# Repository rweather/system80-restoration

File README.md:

Dick Smith System 80 Restoration
================================

This repository chronicles my exploits in restoring a Dick Smith System 80
that I got off eBay.

## Technical specifications

* Z-80 8-bit CPU, running at 1.77MHz.
* 12K of ROM containing BASIC.
* 1K of video RAM for 64 x 16 text mode or 128 x 48 graphics mode.
* 16K of user program RAM, expandable to 48K using an expansion module.

### Initial condition of the unit

According to the seller on eBay, the unit had been sitting in a shed for
30+ years.  The original owner is into boating.  I'm guessing the shed
was near the seaside from the corrosion inside!

The unit was in pretty rough shape cosmetically.  Lots of dirt, cable burns,
missing cassette stickers for play/pause/stop/etc, and broken pieces in the
ventilation at the back (right-click and open in a new tab for a
larger version):

The bottom was in relatively good condition with some cable burns
The nameplate sticker was missing but the serial number and QA stickers
were still present.  Serial number 281001.

Here are some closeups of the outside:

Inside was a lot of dirt and rust!

The cassette mechanism was completely rusted out and the motor was seized up.
Not sure what I can do about this at the moment.

### Cleaning

I pulled everything apart and cleaned the case and keyboard as best
as possible.  Something needs to be done about the cable burns and the
broken pieces later.

### Chip testing

Next, I pulled all of the chips that were in sockets and ran them through my
[BackBit Chip Tester Pro V2](https://store.backbit.io/product/chip-tester/).

Main board:

* Z5 - Z-80 CPU - Failed with "BAD ADDR" error.  I already had a replacement.
* Z10 - E3001 BASIC ROM - Good when tested with chip type "2332".
* Z11 - E3002 BASIC ROM - Good when tested with chip type "2332".
* Z12 - E3003 BASIC ROM - Good when tested with chip type "2332".
* Z27 - HM4716AP-4N 16Kx1 Dynamic RAM - Not testable.
* Z28 - HM4716AP-4N 16Kx1 Dynamic RAM - Not testable.
* Z29 - HM4716AP-4N 16Kx1 Dynamic RAM - Not testable.
* Z30 - HM4716AP-4N 16Kx1 Dynamic RAM - Not testable.
* Z31 - HM4716AP-4N 16Kx1 Dynamic RAM - Not testable.
* Z32 - HM4716AP-4N 16Kx1 Dynamic RAM - Not testable.
* Z33 - HM4716AP-4N 16Kx1 Dynamic RAM - Not testable.
* Z34 - HM4716AP-4N 16Kx1 Dynamic RAM - Not testable.

I wasn't able to test the DRAM chips because I need an adapter to provide the
-5V and +12V supply rails, which I do not presently have.  But since BASIC
ran fine later (see below), I'm guessing the DRAM's are ok.

Video board:

* Z17 - MM2114-N 1Kx4 Static RAM - Good.
* Z18 - MM2114-N 1Kx4 Static RAM - Good.
* Z25 - 52116 Character Generator ROM - Good when tested with chip type "2532".

The dumped ROM images are in the `ROMs` directory of this repository.

In the process of inspecting the PCB's and testing the chips, I found a
dead bug hiding under one of the capacitors.  Which I removed of course.
Don't want the bug causing issues for me later like the
[world's first computer bug](https://www.computerhistory.org/tdih/september/9/).

## Recapping the power supply

This was the initial state of the power supply:

Other than the dirt, the only glaring issue was the three big electrolytic
capacitors.  The date codes on the chips on the motherboard are from 1981,
so these capacitors are around 45 years old.  I didn't even bother to
test them - I just replaced them.

The three original capacitors were:

* 22000uF, 16V - replaced with two 10000uF, 16V capacitors in parallel.
* 2200uF, 25V
* 1000uF, 25V

The voltage outputs seemed fine if a little high.  Probably due to no load.
It was time to power on the main PCB's.

## Power on smoke test

I reconnected everything except the cassette deck, crossed my fingers,
and turned it on.  The LED's on either side of the keyboard turned on.
That's a good sign.

The 5V rail on the CPU board was 5.05V.  On the video board it was 4.99V.
12V rail was 12.15V.  -5V rail was -5.06V.  Perfect.

The 10.64MHz crystal was oscillating at 10.64MHz according to my
oscilloscope.  Also perfect.

The ROM chips were running a little hot.  Not sure if that is a problem
or not yet.

I could see a composite video signal of some sort on the monitor output
port with my oscilloscope.  But my RetroTink had difficulty locking
onto the signal to display an image.  Then I saw a "Ready?" prompt!  Yay!

The video cuts in and out which is very annoying, but I was able to test
the keyboard.  Some of the keys don't work or are intermittent and bouncy.
I did manage to type a simple `10 PRINT "HELLO WORLD"` program once,
but didn't get a photo.  Some keys like T and N only work now and then.

### What's working so far?

* Power supply.
* Z-80 CPU (after I replaced it as described above).
* BASIC ROM's.
* 16K of dynamic RAM on the CPU board.
* 1K of static RAM on the video board.
* Video circuitry for HSYNC/VSYNC and video memory address generation.
* Character generator ROM.
* Composite video output.
* Most keys on the keyboard work, but some keys are flaky.

### In-depth testing and fault finding

Next steps:

* The video signal is not stable; it cuts in and out.
* Deal with the keys on the keyboard that are intermittent or bouncy.
* ROM's run a little hot.  Probably OK.
* Deal with the corrosion on the expansion port connector and keyboard.
* Deal with the cassette deck - it may be a lost cause.

### Flaky video signal

My brother found a composite-to-RGB converter for cheap at an end of
financial year sale for a local electronics retailer.  The composite-to-RGB
converter didn't work with other computers like my Dick Smith Cat,
but it worked perfectly with the System 80!

It looks like the video problem was with the RetroTink all along,
not with the System 80.

The video is a little shaky, but I can live with it for now.

### Non-working keys on the keyboard

I found the problem with the keyboard.  With all of the handling of the PCB,
metal fatigue in the wires built up and snapped two of the wires on the
keyboard ribbon cable (right-click and open in a new tab for a larger version):

This type of soldered ribbon cable is a real pain in the neck.
Even minor board handling will tear them off if you aren't careful.
There were similar cables on
[a VZ200 and a VZ300 that I restored previously](https://github.com/rweather/vz200-restoration).

Those two wires correspond to the columns containing the intermittent
keys like N and T.  No wonder I was having problems typing "PRINT" in BASIC.
I was able to type in a "HELLO WORLD" BASIC program just one time.
I guess the cable was angled to make the wires touch briefly that one time.

I replaced the cable with something easier to repair in the future if a
wire comes loose:

I then tested all of the keys.  Some of them were very flaky.  Testing
them with a multimeter showed some at 20 Mohms when pressed.  Probably
corrosion in the contacts.  I pounded the keys a few dozen times and
they came good!

Some keys like N and I are still a little bouncy, but as long as I don't
type too fast they are ok.  Unfortunately, my natural typing speed is fast!

### Summary of changes made

Here is a summary of the changes that I made:

* Cleaned the case, keyboard, PCB's, etc.
* Replaced the filter capacitors in the power supply.
* Replaced the Z-80 CPU with a new one, as the original was broken.
* Desoldered the RF video cable from the RF modulator.  Analog television
  sets are very rare these days and composite video works fine.
* Modified the keyboard ribbon cable and connectors to be easily repairable.

Costs (in AUD):

* $500 for the System 80 off eBay.
* $27 to replace the filter capacitors in the power supply.

## Schematics

I have reproduced some of the schematics from the Technical Manual in KiCad
and generated PDF versions.  The original schematics can be hard to read.

* [System 80 Main Board](schematics/System_80_Main_Board/PDF/System_80_Main_Board.pdf)
* [System 80 Video / Cassette Board](schematics/System_80_Video_Cassette/PDF/System_80_Video_Cassette.pdf)
* [System 80 Power Supply](schematics/System_80_Power_Supply/PDF/System_80_Power_Supply.pdf)
* [System 80 Keyboard](schematics/System_80_Keyboard/PDF/System_80_Keyboard.pdf)

## Expansion options

I designed a [Memory Cartridge](memory_cartridge.md) for the System 80
that plugs into the expanion bus.  It provides either 32K of extra RAM,
or 16K of RAM plus 16K of EEPROM.

## Adapting the schematic

In theory the KiCad schematics could be modernised and then laid out on
brand new PCB's.  But a lot of work would be required to add footprints
and lay everything out.

The components in the System 80 are mostly bog-standard Z-80, memory, and
TTL logic chips that can still be sourced today.  The main exception is
the character generator ROM, but that could be replaced with a modern EEPROM.

Making a new System 80 from scratch wouldn't be difficult.  But some things
would be easier with modern components:

* Use a single 16K EEPROM instead of separate 4K EPROM's.
* Use static RAM chips like the 32K 62256 for system memory, instead of
dynamic RAM.  This removes a lot of complexity from the memory interface.
* Replace the 6-way 74LS367 bus transceivers with the 8-way 74LS244 and
74LS245 instead to reduce the number of transceiver chips.
* Replace the 5-pin composite video connector with a standard RCA jack.
* Replace the character generator ROM with a modern EEPROM and include the
graphics characters in the EEPROM.  This removes the need for a separate
circuit for rendering the graphics characters.

## License

<p xmlns:cc="http://creativecommons.org/ns#" xmlns:dct="http://purl.org/dc/terms/"><span property="dct:title">System 80 Restoration</span> by <span property="cc:attributionName">Rhys Weatherley</span> is licensed under <a href="http://creativecommons.org/licenses/by-nc-sa/4.0/?ref=chooser-v1" target="_blank" rel="license noopener noreferrer" style="display:inline-block;">Attribution-NonCommercial-ShareAlike 4.0 International</a></p>

## Contact

For more information on this project, to report bugs, or to suggest
improvements, please contact the author Rhys Weatherley via
[email](mailto:rhys.weatherley@gmail.com).

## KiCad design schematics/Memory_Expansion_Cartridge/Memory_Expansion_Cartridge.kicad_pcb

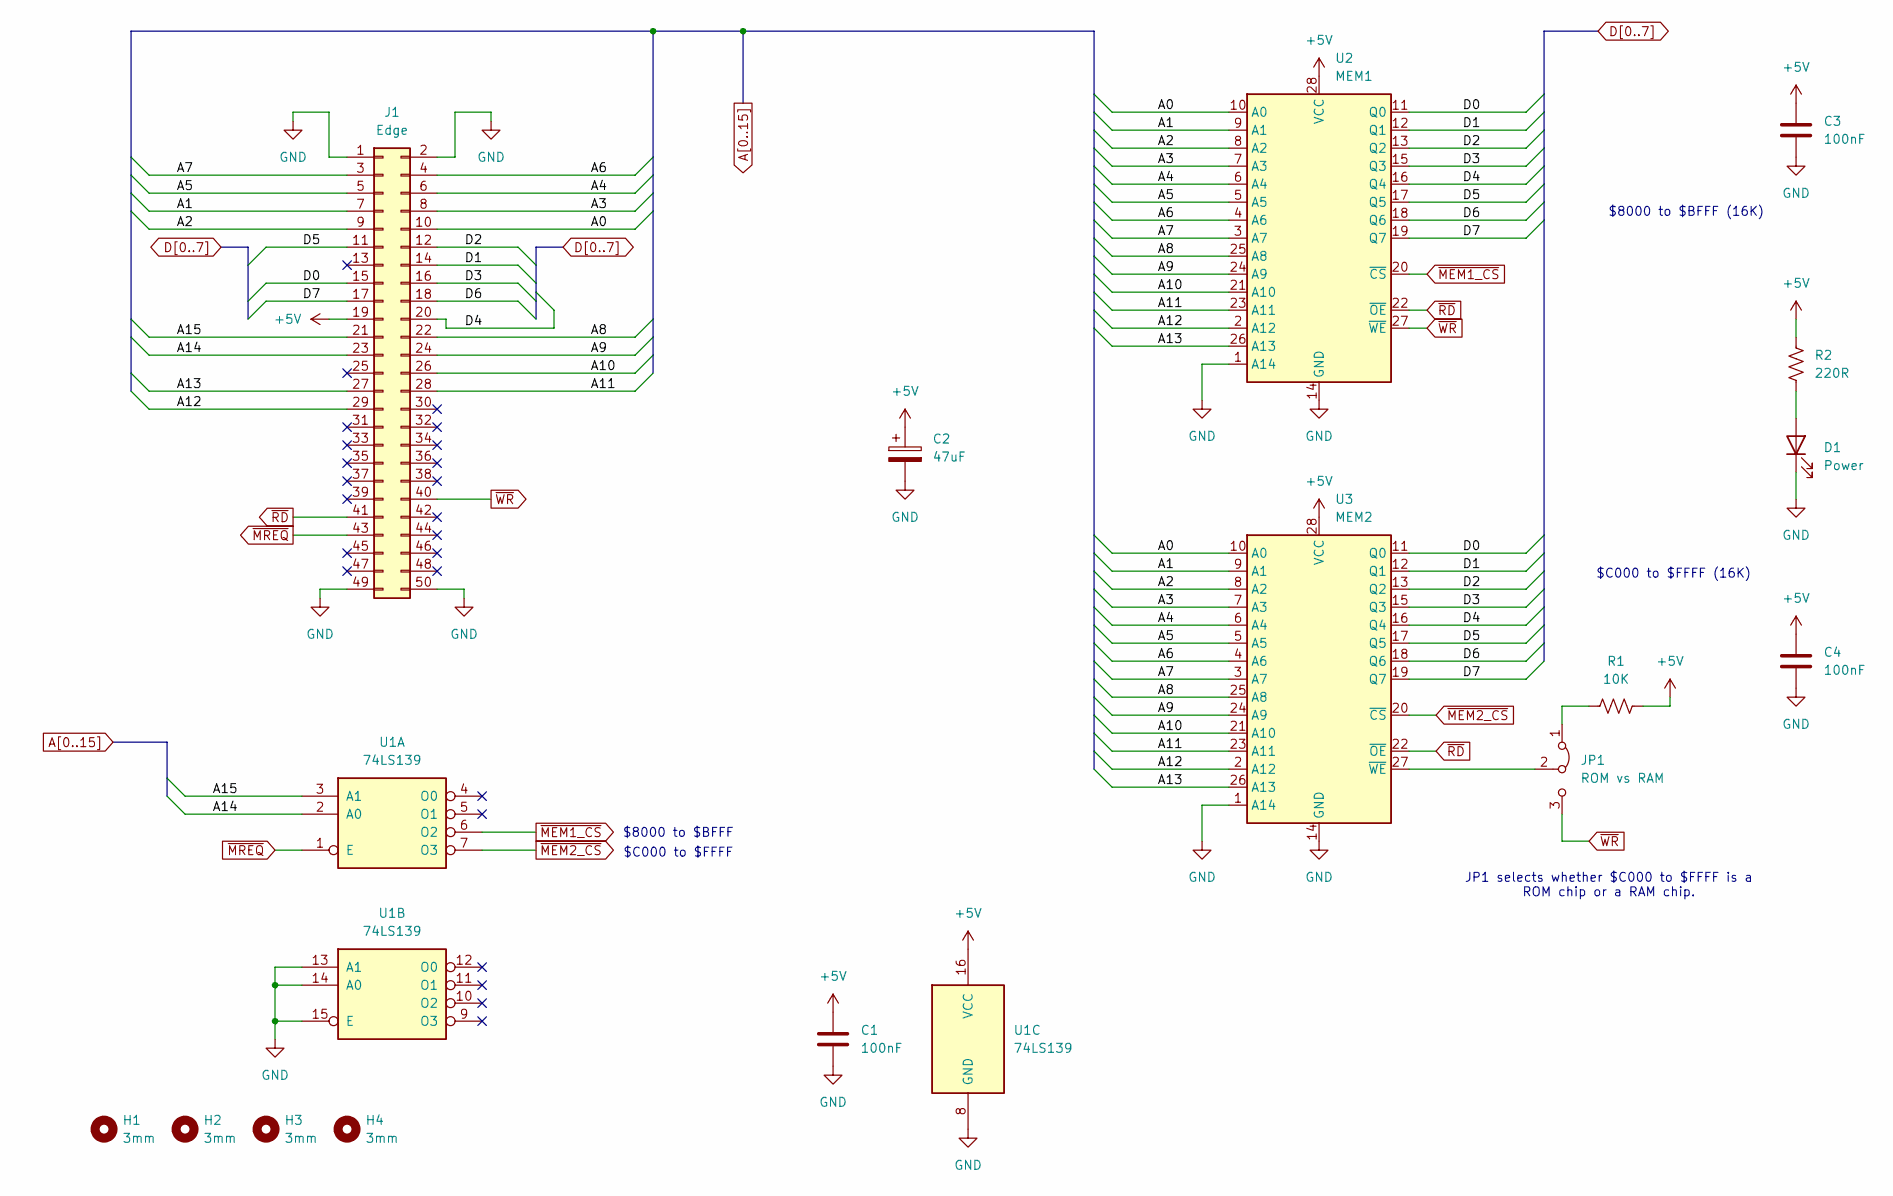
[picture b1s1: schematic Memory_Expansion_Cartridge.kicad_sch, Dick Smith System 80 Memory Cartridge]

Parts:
C1, C3, C4: 100nF; C_Disc_D5.0mm_W2.5mm_P5.00mm
C2: 47uF; CP_Radial_D6.3mm_P2.50mm
D1: Power; LED_D5.0mm
H1, H2, H3, H4: 3mm; MountingHole_3mm
J1: Edge; Edge_Connector_50pin
JP1: ROM vs RAM; PinHeader_1x03_P2.54mm_Vertical
R1: 10K; R_Axial_DIN0207_L6.3mm_D2.5mm_P10.16mm_Horizontal
R2: 220R; R_Axial_DIN0207_L6.3mm_D2.5mm_P10.16mm_Horizontal
U1: 74LS139; DIP-16_W7.62mm
U2: MEM1; DIP_Socket-28_W11.9_W12.7_W15.24_W17.78_W18.5_3M_228-1277-0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
U3: MEM2; DIP_Socket-28_W11.9_W12.7_W15.24_W17.78_W18.5_3M_228-1277-0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

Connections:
+5V: C1.1, C2.1, C3.1, C4.1, J1.19, R1.2, R2.1, U1.16 (VCC), U2.28 (VCC), U3.28 (VCC)
A0: J1.10, U2.10 (A0), U3.10 (A0)
A1: J1.7, U2.9 (A1), U3.9 (A1)
A2: J1.9, U2.8 (A2), U3.8 (A2)
A3: J1.8, U2.7 (A3), U3.7 (A3)
A4: J1.6, U2.6 (A4), U3.6 (A4)
A5: J1.5, U2.5 (A5), U3.5 (A5)
A6: J1.4, U2.4 (A6), U3.4 (A6)
A7: J1.3, U2.3 (A7), U3.3 (A7)
A8: J1.22, U2.25 (A8), U3.25 (A8)
A9: J1.24, U2.24 (A9), U3.24 (A9)
A10: J1.26, U2.21 (A10), U3.21 (A10)
A11: J1.28, U2.23 (A11), U3.23 (A11)
A12: J1.29, U2.2 (A12), U3.2 (A12)
A13: J1.27, U2.26 (A13), U3.26 (A13)
A14: J1.23, U1.2 (A0)
A15: J1.21, U1.3 (A1)
D0: J1.15, U2.11 (Q0), U3.11 (Q0)
D1: J1.14, U2.12 (Q1), U3.12 (Q1)
D2: J1.12, U2.13 (Q2), U3.13 (Q2)
D3: J1.16, U2.15 (Q3), U3.15 (Q3)
D4: J1.20, U2.16 (Q4), U3.16 (Q4)
D5: J1.11, U2.17 (Q5), U3.17 (Q5)
D6: J1.18, U2.18 (Q6), U3.18 (Q6)
D7: J1.17, U2.19 (Q7), U3.19 (Q7)
GND: C1.2, C2.2, C3.2, C4.2, D1.1 (K), J1.1, J1.2, J1.49, J1.50, U1.8 (GND), U1.13 (A1), U1.14 (A0), U1.15 (E), U2.1 (A14), U2.14 (GND), U3.1 (A14), U3.14 (GND)
unnamed: D1.2 (A), R2.2
unnamed: JP1.1 (A), R1.1
unnamed: JP1.2 (C), U3.27 (~WE)
~MEM1_CS: U1.6 (O2), U2.20 (~CS)
~MEM2_CS: U1.7 (O3), U3.20 (~CS)
~MREQ: J1.43, U1.1 (E)
~RD: J1.41, U2.22 (~OE), U3.22 (~OE)
~WR: J1.40, JP1.3 (B), U2.27 (~WE)

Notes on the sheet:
$C000 to $FFFF (16K)
JP1 selects whether $C000 to $FFFF is a ROM chip or a RAM chip.
$8000 to $BFFF (16K)
$C000 to $FFFF
$8000 to $BFFF

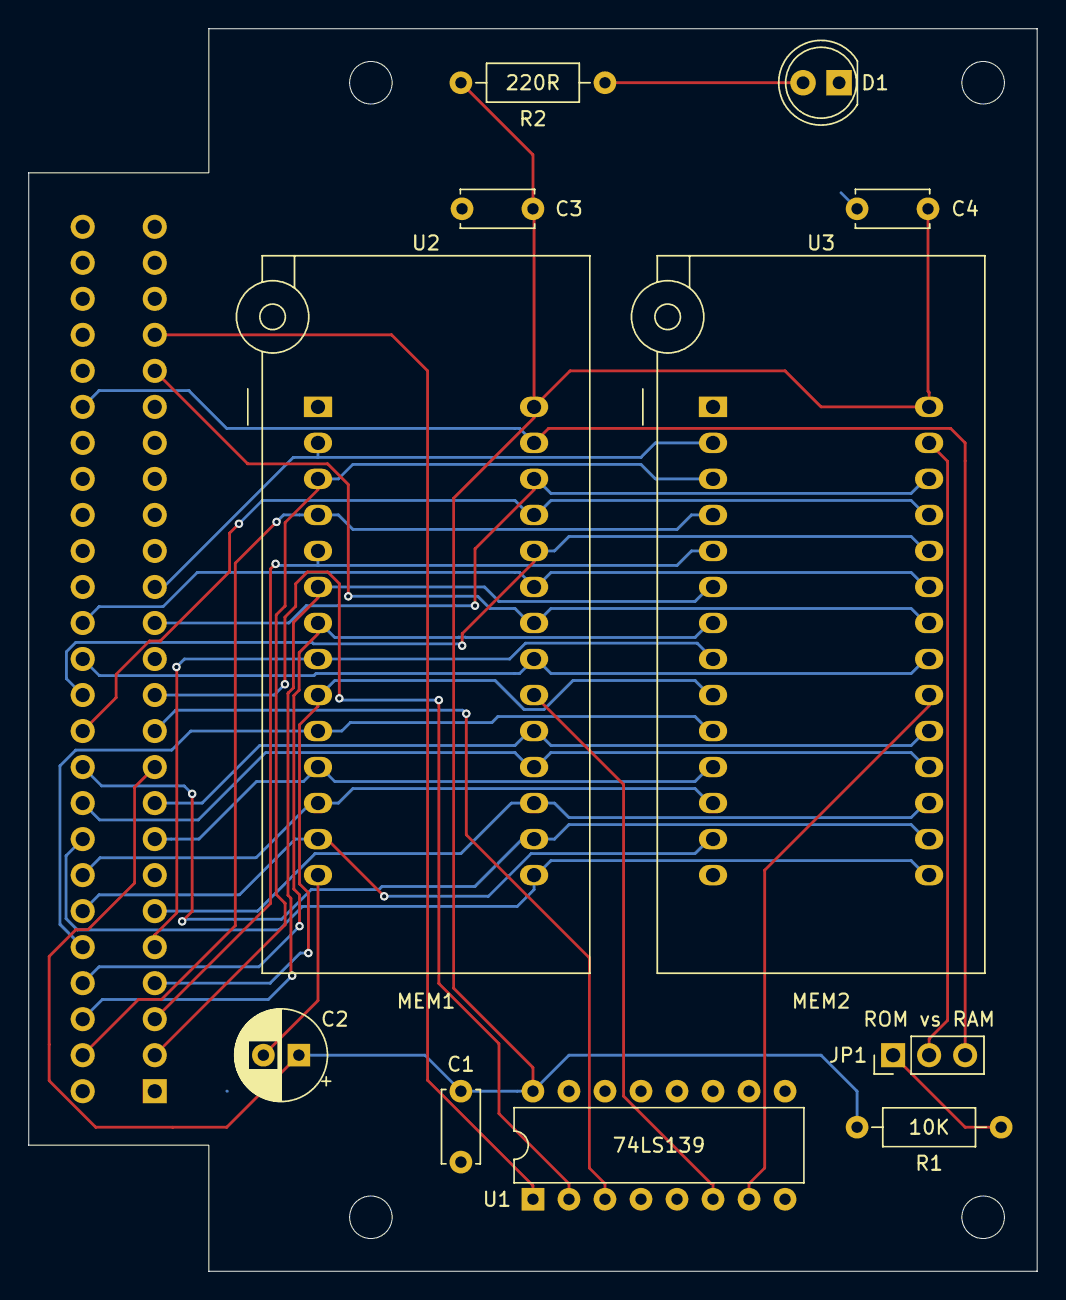
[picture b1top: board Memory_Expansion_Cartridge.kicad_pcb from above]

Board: 2 copper layers, 71.1 x 87.6 mm, 16 parts (1 on the bottom side), 34 nets.

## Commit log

2025-01-04 Schematic for the System 80 main board
2025-01-04 Schematic for System 80 power supply
2025-01-12 Schematic for the System 80 video/cassette board
2025-01-19 Test the socketed chips and dump the ROM's
2025-01-26 Fix the CPU clock frequency: 1.77MHz, not 1.79MHz
2025-01-26 Description and photos of the work done so far
2025-06-16 Update: video is working with an alternative converter
2025-06-21 Keyboard ribbon cable is now fixed
2025-06-21 Diagram showing the arrangement of pins on the expansion edge connector
2025-07-27 Memory Cartridge Design
2025-07-27 Add a note about problems inserting the memory cartridge

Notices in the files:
schematics/Memory_Expansion_Cartridge/Memory_Expansion_Cartridge.kicad_pcb:
Copyright (c) 2025 Rhys Weatherley
